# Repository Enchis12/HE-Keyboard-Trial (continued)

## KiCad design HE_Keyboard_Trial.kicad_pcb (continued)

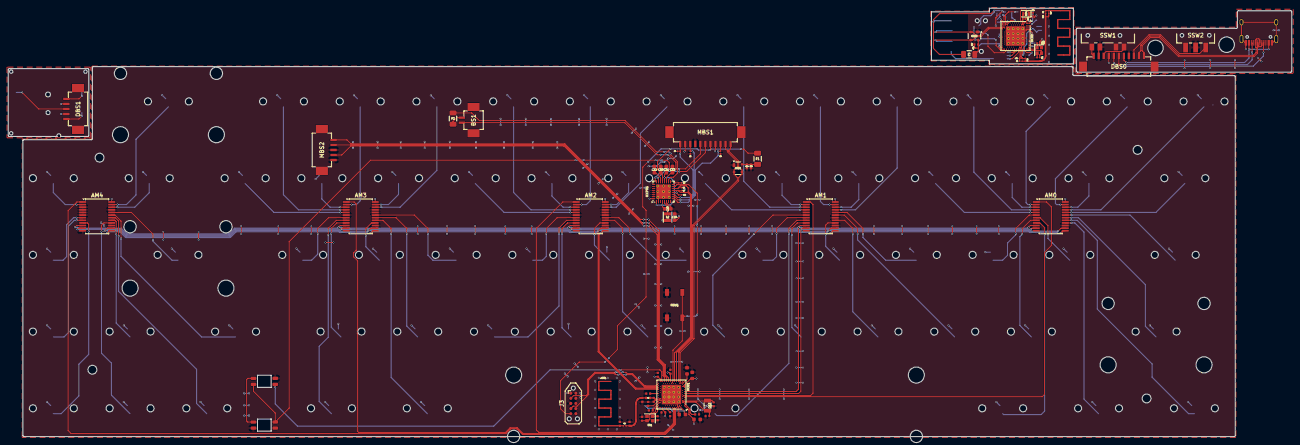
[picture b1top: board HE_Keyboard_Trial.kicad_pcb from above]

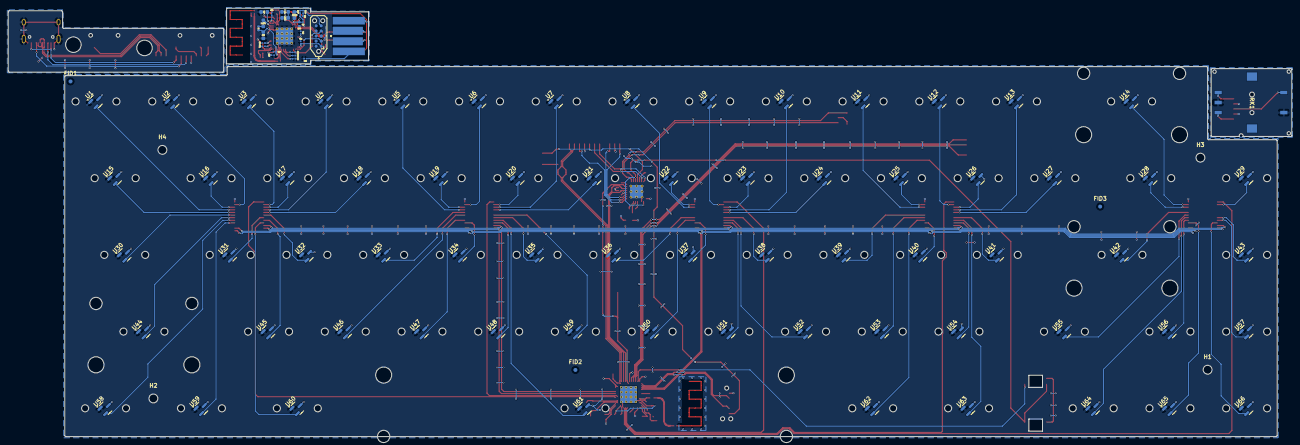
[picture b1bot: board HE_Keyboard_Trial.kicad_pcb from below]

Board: 2 copper layers, 318.6 x 106.3 mm, 246 parts (165 on the bottom side), 158 nets.

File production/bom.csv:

Designator,Footprint,Quantity,Value,LCSC Part #
"AM0, AM1, AM2, AM3, AM4",SSOP-24_5.3x8.2mm_P0.65mm,5,CD74HC4067SM,C98457
"ANT1, ANT2",MIFA,2,~,
BS1,Hong_Cheng_HCZZ0001-2,1,HCZZ0001-2,C7433453
"C1, C10, C19, C8, C9",Capacitor_0402,5,100nF,
"C11, C14, C16, C17",Capacitor_0402,4,12pF,
C12,Capacitor_0402,1,0.8pF,
C13,Capacitor_0402,1,0.5pF,
C18,Capacitor_0402,1,1µF,
C2,Capacitor_0402,1,100pF,
"C20, C21, C24",Capacitor_0603,3,10µF,
"C22, C25, C36, C4, C43, C6",Capacitor_0603,6,1µF,
C23,Capacitor_0603,1,2.2µF,
"C26, C33, C49, C50, C51, C53, C59",0201,7,100nF,
"C27, C28, C29",Capacitor_0402,3,N.C.,
C3,Capacitor_0402,1,820pF,
C30,Capacitor_0402,1,1.5pF,
"C31, C32, C41, C42",0201,4,12pF,
"C34, C40, C46, C57",0201,4,N.C.,
C35,0201,1,100pF,C710791
C37,0201,1,47nF,
C38,0201,1,820pF,
"C39, C48, C5, C7",Capacitor_0603,4,4.7µF,
C44,0201,1,0.8pF,
C45,0201,1,0.5pF,C2981049
C47,0201,1,1.5pF,
"C52, C54",Capacitor_0402,2,4.7µF,
C58,0201,1,10nF,
"CR1, CR3",Murata_Crystal_SMD_2016-4Pin_2.0x1.6mm,2,32MHz,C914155
CR2,Crystal_SMD_3215-2Pin_3.2x1.5mm,1,32.768kHz,C97605
CR4,Crystal_SMD_2012-2Pin_2.0x1.2mm,1,32.768kHz,C97603
"DBS0, MBS1",Hong_Cheng_HCZZ0001-11,2,HCZZ0001-11,C7433462
"DBS1, MBS2",Hong_Cheng_HCZZ0001-5,2,HCZZ0001-5,C7433456
"ESD1, ESD2",SOT-143,2,PRTR5V0U2X,C41409257
"F1, F2, F3",1206,3,500mA,C269112
"FB3, FB4",0201,2,120R/0.85A,C2661865
"FID1, FID2, FID3",Fiducial_1mm_Mask2mm,3,Fiducial,
"H1, H2, H3, H4",MountingHole_2.2mm_M2,4,MountingHole,
ICCPR1,Nordic_QFN-32-1EP_5x5mm_P0.5mm_EP3.6x3.6mm_ThermalVias,1,nPM1300 Datasheet Layout,C7501206
J1,USB A,1,USB_A,
"J2, J3",Tag-Connect_TC2050-IDC-NL_2x05_P1.27mm_Vertical,2,TC2050-IDC,
L1,0402,1,4.7nH,C3249625
L2,Samsung_CIGT201610EH2R2MNE,1,2.2µH,C5185544
L3,0201,1,4.7nH,C86126
"L4, L5",0603,2,10µH,C87216
L6,0402,1,15nH,C87189
"LED1, LED2",LED_SK6812MINI,2,LED_SK6812MINI,C5149201
MCU1,Nordic_AQFN-73-1EP_7x7mm_P0.5mm_Thermal,1,nRF52840 aQFN73 Datasheet Layout,C190794
MCU2,Nordic_AQFN-73-1EP_7x7mm_P0.5mm_Thermal,1,nRF52840 aQFN73 Datasheet Layout,
"R1, R9",0201,2,0R,
R2,0201,1,4R7,
R3,0201,1,250-500k,
"R4, R5, R6, R7, R8",0201,5,10k,
RK1,RotaryEncoder_CTR_ED11601M-FB15A7.0-C15-202,1,RotaryEncoder_Switch_MP,
RSW1,Button_TL3342,1,Switch,C2886897
SSW1,SW_SP3T_Korean_Hroparts_Elec_K3-1346S-K1,1,K3-1346S-K1,
SSW2,SW_SPDT_Korean_Hroparts_Elec_K3-1280S-K1,1,K3-1280S-K1,
"U1, U10, U11, U12, U13, U14, U15, U16, U17, U18, U19, U2, U20, U21, U22, U23, U24, U25, U26, U27, U28, U29, U3, U30, U31, U32, U33, U34, U35, U36, U37, U38, U39, U4, U40, U41, U42, U43, U44, U45, U46, U47, U48, U49, U5, U50, U51, U52, U53, U54, U55, U56, U57, U58, U59, U6, U60, U61, U62, U63, U64, U65, U66, U7, U8, U9",GH39FKSW_OH49E-S,66,Hall_Sensor,C266230
USBC1,USB_C_HRO_TYPE-C-31-M-12,1,USB_C_Receptacle_USB2.0_14P,C165948

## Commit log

2024-12-25 Second Commit
    new wiring and label
2024-12-28 Third Commit
    Kinda add some little changes but still confused on how using the nPM1300
2024-12-28 Fourth Commit
    changing some name to not get sued :v
2024-12-31 Fifth Commit
    updating track width and via's diameter
2025-01-08 Sixth Commit
    Almost done. Just need to make sure the field zone and each pin is connected properly
2025-01-18 7th Commit
    Adding the reduced nRF52840 dongle and some minor tweak
2025-01-19 8th commit
    Some minor tweak
2025-01-19 9th commit
    minor tweak
2025-02-14 9th commit
    some minor tweak + adding production files
